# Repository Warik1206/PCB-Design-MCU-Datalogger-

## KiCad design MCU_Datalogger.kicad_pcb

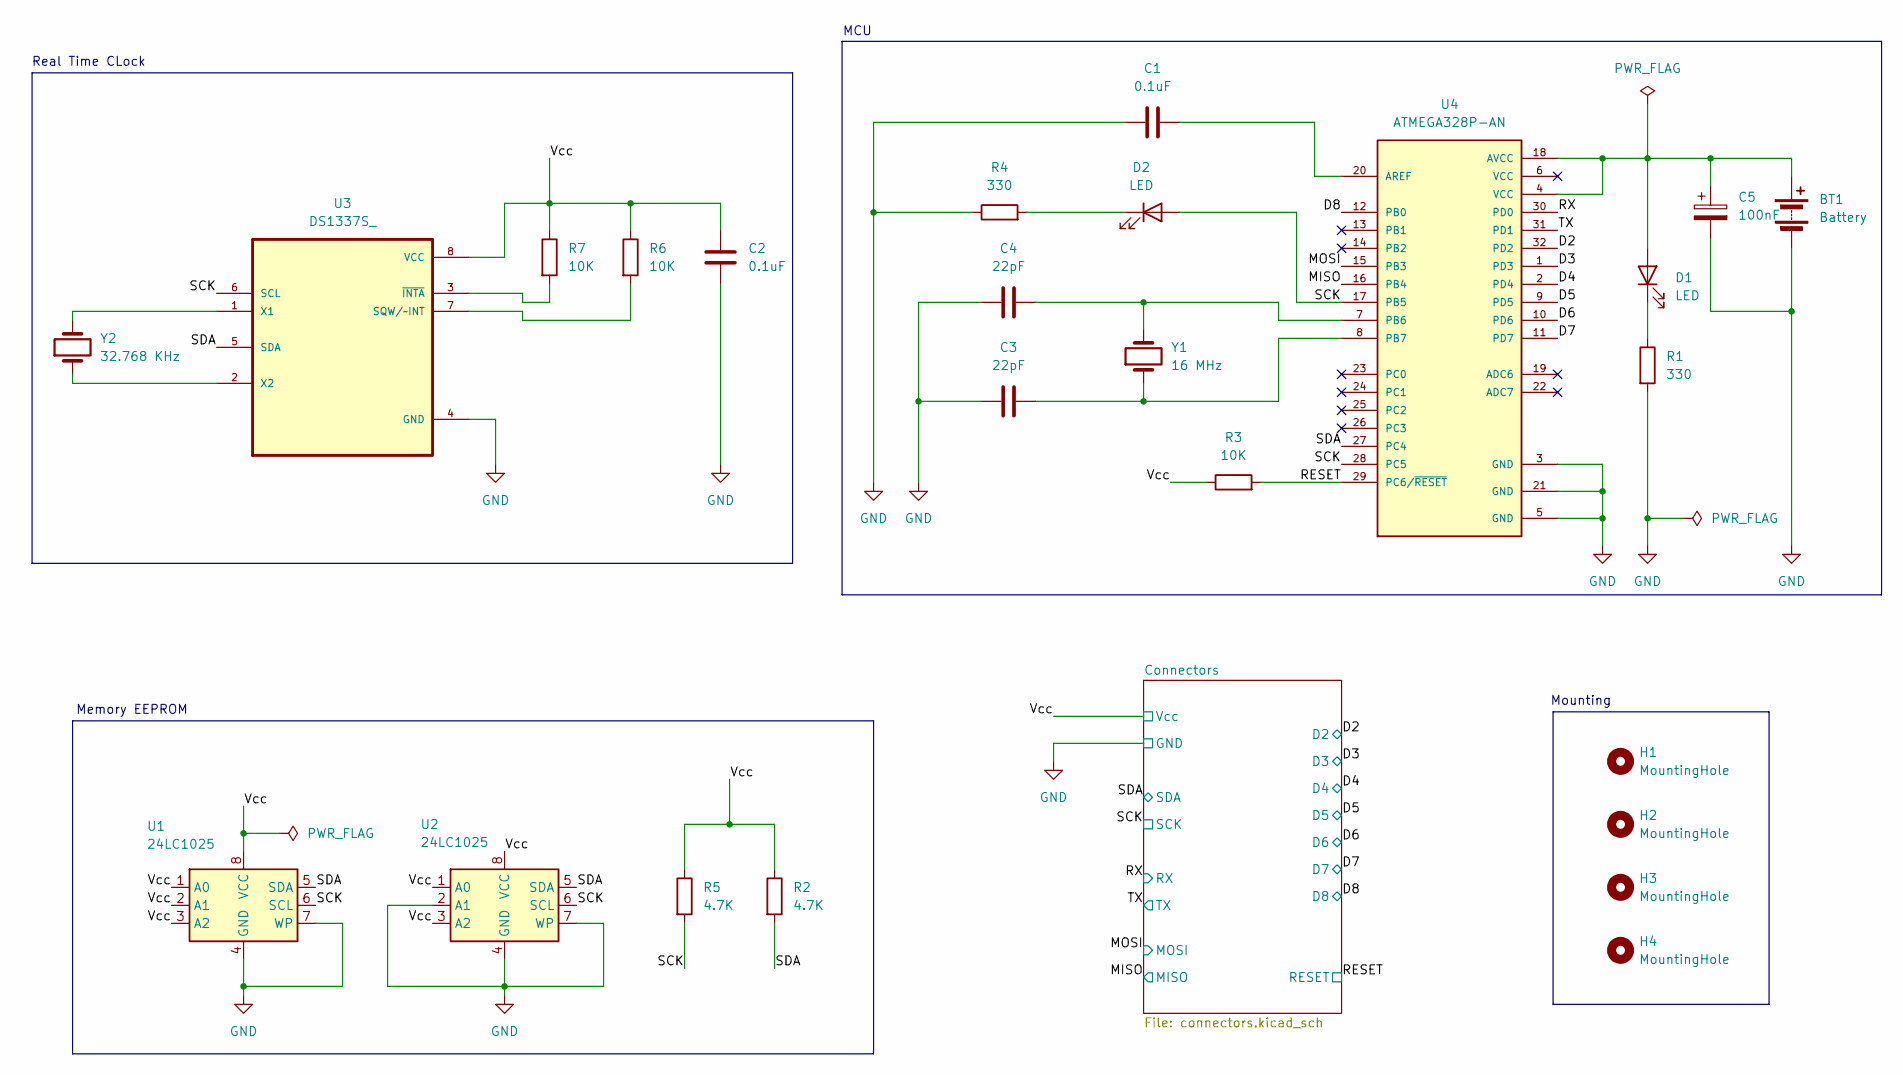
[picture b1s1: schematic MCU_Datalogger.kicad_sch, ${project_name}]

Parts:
BT1: Battery; PinHeader_1x02_P2.54mm_Vertical
C1, C2: 0.1uF; C_0805_2012Metric
C3, C4: 22pF; C_0805_2012Metric
C5: 100nF; C_0805_2012Metric
D1, D2: LED; LED_0805_2012Metric
H1, H2, H3, H4: MountingHole; MountingHole_2.1mm
R1, R4: 330; R_0805_2012Metric
R2, R5: 4.7K; R_0805_2012Metric
R3, R6, R7: 10K; R_0805_2012Metric
U1, U2: 24LC1025; SOIC-8_5.23x5.23mm_P1.27mm
U3: DS1337S_; SOIC127P600X175-8N
U4: ATMEGA328P-AN; QFP80P900X900X120-32N
Y1: 16 MHz; Crystal_SMD_5032-2Pin_5.0x3.2mm_HandSoldering
Y2: 32.768 KHz; Crystal_SMD_5032-2Pin_5.0x3.2mm_HandSoldering

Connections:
/D2: U4.32 (PD2); also elsewhere on the board
/D3: U4.1 (PD3); also elsewhere on the board
/D4: U4.2 (PD4); also elsewhere on the board
/D5: U4.9 (PD5); also elsewhere on the board
/D6: U4.10 (PD6); also elsewhere on the board
/D7: U4.11 (PD7); also elsewhere on the board
/D8: U4.12 (PB0); also elsewhere on the board
/MISO: U4.16 (PB4); also elsewhere on the board
/MOSI: U4.15 (PB3); also elsewhere on the board
/RESET: R3.2, U4.29 (PC6/~RESET); also elsewhere on the board
/RX: U4.30 (PD0); also elsewhere on the board
/SCK: D2.2 (A), R5.2, U1.6 (SCL), U2.6 (SCL), U3.6 (SCL), U4.17 (PB5), U4.28 (PC5); also elsewhere on the board
/SDA: R2.2, U1.5 (SDA), U2.5 (SDA), U3.5 (SDA), U4.27 (PC4); also elsewhere on the board
/TX: U4.31 (PD1); also elsewhere on the board
/Vcc: C2.1, R2.1, R3.1, R5.1, R6.1, R7.1, U1.1 (A0), U1.2 (A1), U1.3 (A2), U1.8 (VCC), U2.1 (A0), U2.3 (A2), U2.8 (VCC), U3.8 (VCC); also elsewhere on the board
GND: BT1.2 (-), C1.1, C2.2, C3.1, C4.1, C5.2, R1.2, R4.1, U1.4 (GND), U1.7 (WP), U2.2 (A1), U2.4 (GND), U2.7 (WP), U3.4 (GND), U4.3 (GND), U4.5 (GND), U4.21 (GND); also elsewhere on the board
unnamed: BT1.1 (+), C5.1, D1.2 (A), U4.4 (VCC), U4.18 (AVCC)
unnamed: D1.1 (K), R1.1
unnamed: D2.1 (K), R4.2
unnamed: R6.2, U3.7 (SQW/~INT)
unnamed: U3.1 (X1), Y2.2
unnamed: U3.2 (X2), Y2.1
unnamed: R7.2, U3.3 (~INTA)
unnamed: C1.2, U4.20 (AREF)
unnamed: C4.2, U4.7 (PB6), Y1.2
unnamed: C3.2, U4.8 (PB7), Y1.1

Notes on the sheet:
Real Time CLock
Mounting
Memory EEPROM
MCU

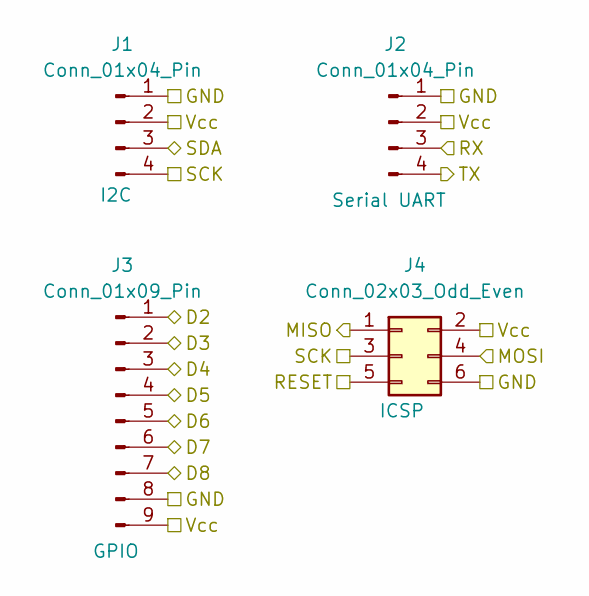
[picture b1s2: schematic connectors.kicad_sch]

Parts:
J1, J2: Conn_01x04_Pin; PinHeader_1x04_P2.54mm_Vertical
J3: Conn_01x09_Pin; PinHeader_1x09_P2.54mm_Vertical
J4: Conn_02x03_Odd_Even; PinHeader_2x03_P2.54mm_Vertical

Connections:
/D2: J3.1; also elsewhere on the board
/D3: J3.2; also elsewhere on the board
/D4: J3.3; also elsewhere on the board
/D5: J3.4; also elsewhere on the board
/D6: J3.5; also elsewhere on the board
/D7: J3.6; also elsewhere on the board
/D8: J3.7; also elsewhere on the board
/MISO: J4.1; also elsewhere on the board
/MOSI: J4.4; also elsewhere on the board
/RESET: J4.5; also elsewhere on the board
/RX: J2.3; also elsewhere on the board
/SCK: J1.4, J4.3; also elsewhere on the board
/SDA: J1.3; also elsewhere on the board
/TX: J2.4; also elsewhere on the board
/Vcc: J1.2, J2.2, J3.9, J4.2; also elsewhere on the board
GND: J1.1, J2.1, J3.8, J4.6; also elsewhere on the board

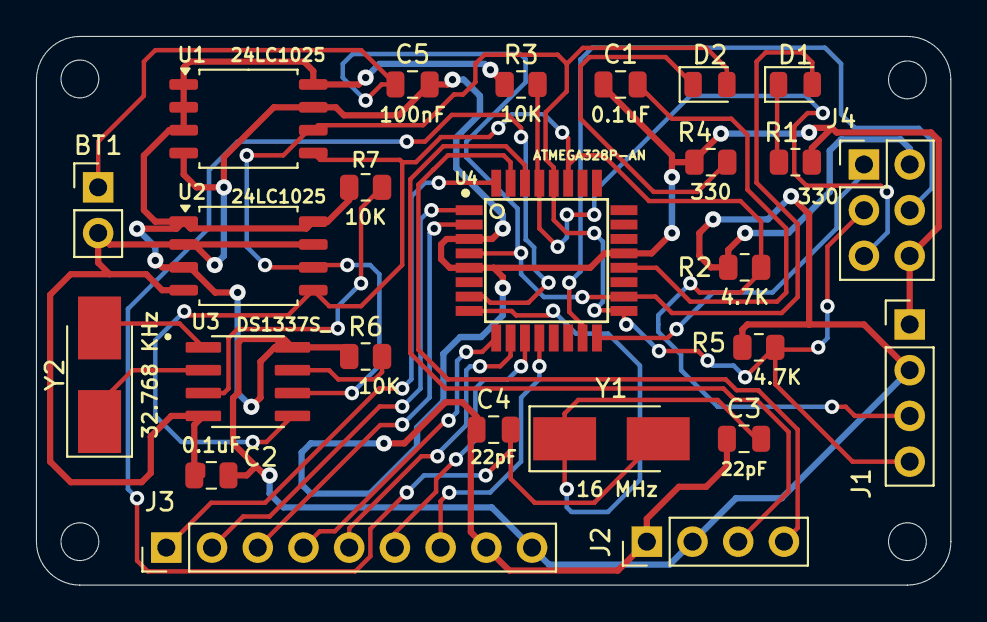
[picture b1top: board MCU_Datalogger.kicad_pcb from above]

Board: 2 copper layers, 50.8 x 30.5 mm, 29 parts (0 on the bottom side), 26 nets.

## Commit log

2025-01-12 First commit of project.
2025-01-12 Setup of EESchema for new Project
2025-01-12 Have added required symbols to the schematic sheets
2025-01-12 Changed locations of symbols.
2025-01-12 Added Component Values.
2025-01-12 Assigned Footprints.
2025-01-12 Finished Wiring of Main Sheet.
2025-01-13 Completed Wiring in second sheet.
2025-01-13 Allocated GND and Vcc nets to the Power Net Class.
2025-01-13 Completed Comments
2025-01-13 Setup PCB New 2 layer.
2025-01-13 Placed Components in 2 layer PCB.
2025-01-13 Two Layer PCB Routing Done.
2025-01-14 Two Layer PCB done along with 3d Models.
2025-01-14 Completed 2 layer PCB MCU along with gerbers.
2025-01-14 Added gerbers to Gitignore.
2025-01-15 Add all Gerber files
